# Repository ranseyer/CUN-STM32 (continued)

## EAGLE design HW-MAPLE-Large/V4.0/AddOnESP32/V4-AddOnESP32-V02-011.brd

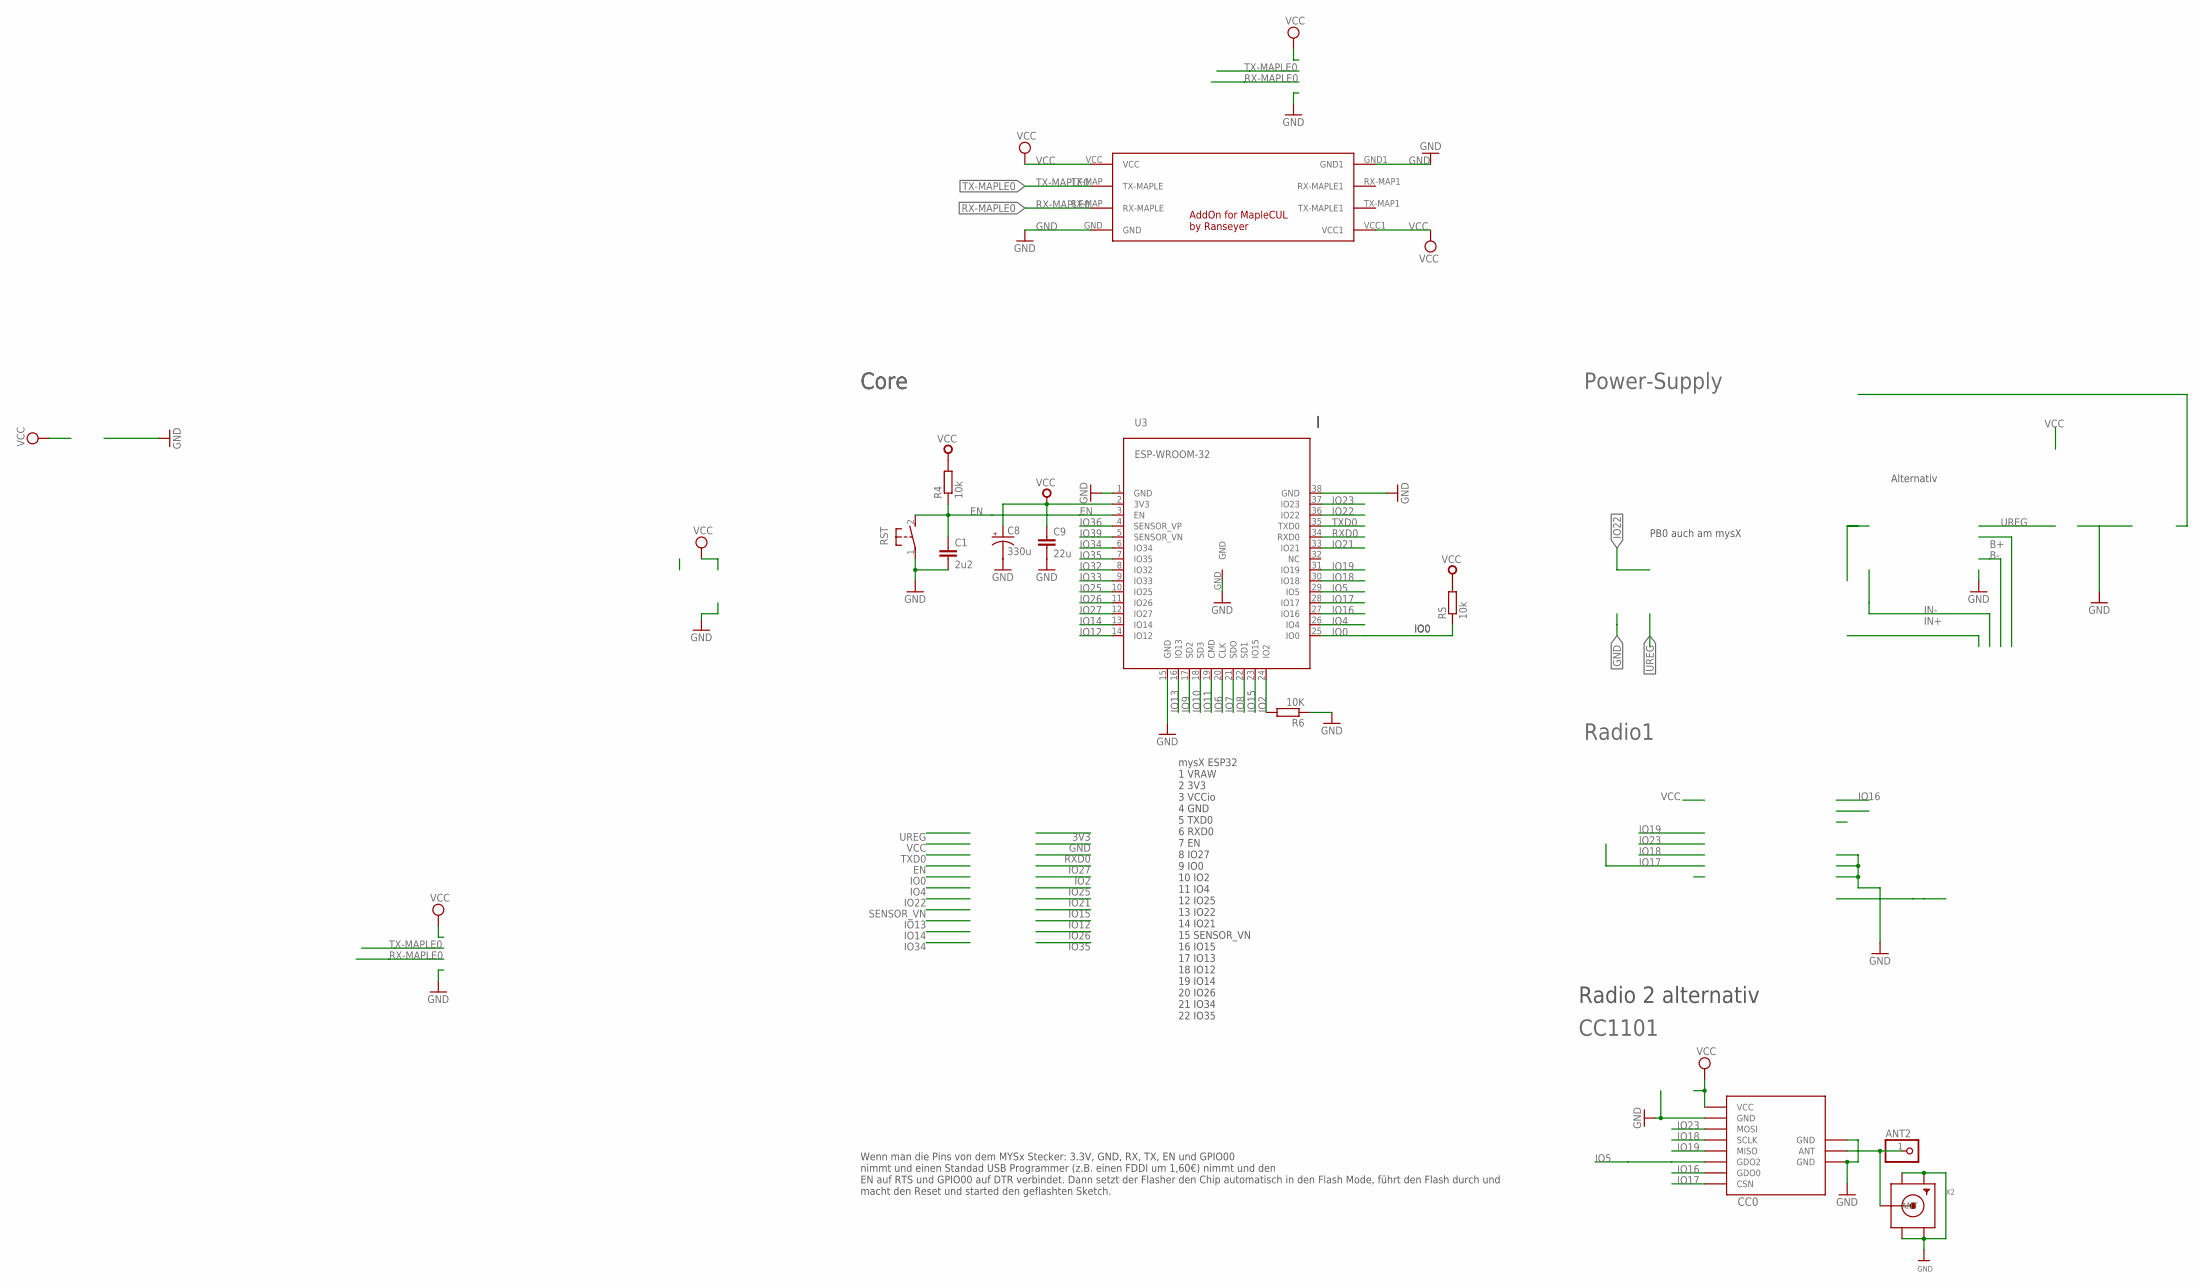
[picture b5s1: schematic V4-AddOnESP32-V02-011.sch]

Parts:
ANT2: PINHD-1X1; 1X01
C1: 2u2; C0805
C8: 330u; VISHAY_C
C9: 22u; C0805
CC0: CC1101; CC1101_MODULE1_SMD
R4, R5: 10k; M0805
R6: 10K; M0805
RST: DTSM-3
U3: ESP-WROOM-32
U$2: MAPLE-CUL-ADDON-V01; MAPLE-CUL-V01
X2: SMACONNECTOR_EDGE; SMA_EDGELAUNCH

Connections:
ANT0: ANT2.1, CC0.ANT, X2.P (ANT)
EN: C1.1, R4.1, RST.2, U3.3 (EN)
GND: C1.2, C8.-, C9.2, CC0.GND@0 (GND), CC0.GND@1 (GND), CC0.GND@2 (GND), R6.1, RST.1, U3.1 (GND), U3.15 (GND), U3.38 (GND), U3.GND, U$2.GND, U$2.GND1, X2.GND@1 (GND4), X2.GND@2 (GND3), X2.GND@3 (GND2), X2.GND@4 (GND1)
IO0: R5.1, U3.25 (IO0)
IO2: R6.2, U3.24 (IO2)
IO4: U3.26 (IO4)
IO5: CC0.GDO2, U3.29 (IO5)
IO6: U3.20 (CLK)
IO7: U3.21 (SDO)
IO8: U3.22 (SD1)
IO9: U3.17 (SD2)
IO10: U3.18 (SD3)
IO11: U3.19 (CMD)
IO12: U3.14 (IO12)
IO13: U3.16 (IO13)
IO14: U3.13 (IO14)
IO15: U3.23 (IO15)
IO16: CC0.GDO0, U3.27 (IO16)
IO17: CC0.CSN, U3.28 (IO17)
IO18: CC0.SCLK, U3.30 (IO18)
IO19: CC0.MISO, U3.31 (IO19)
IO21: U3.33 (IO21)
IO22: U3.36 (IO22)
IO23: CC0.MOSI, U3.37 (IO23)
IO25: U3.10 (IO25)
IO26: U3.11 (IO26)
IO27: U3.12 (IO27)
IO32: U3.8 (IO32)
IO33: U3.9 (IO33)
IO34: U3.6 (IO34)
IO35: U3.7 (IO35)
IO36: U3.4 (SENSOR_VP)
IO39: U3.5 (SENSOR_VN)
RX-MAPLE0: U$2.RX-MAP (RX-MAPLE)
RXD0: U3.34 (RXD0)
TX-MAPLE0: U$2.TX-MAP (TX-MAPLE)
TXD0: U3.35 (TXD0)
VCC: C8.+, C9.1, CC0.VCC, R4.2, R5.2, U3.2 (3V3), U$2.VCC, U$2.VCC1

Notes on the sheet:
mysX ESP32 1 VRAW 2 3V3 3 VCCio 4 GND 5 TXD0 6 RXD0 7 EN 8 IO27 9 IO0 10 IO2 11 IO4 12 IO25 13 IO22 14 IO21 15 SENSOR_VN 16 IO15 17 IO13 18 IO12 19 IO14 20 IO26 21 IO34 22 IO35
PB0 auch am mysX
Radio1
Radio 2 alternativ
CC1101
Wenn man die Pins von dem MYSx Stecker: 3.3V, GND, RX, TX, EN und GPIO00 nimmt und einen Standad USB Programmer (z.B. einen FDDI um 1,60€) nimmt und den EN auf RTS und GPIO00 auf DTR verbindet. Dann setzt der Flasher den Chip automatisch in den Flash Mode, führt den Flash durch und macht den Reset 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
Alternativ
Core
Power-Supply

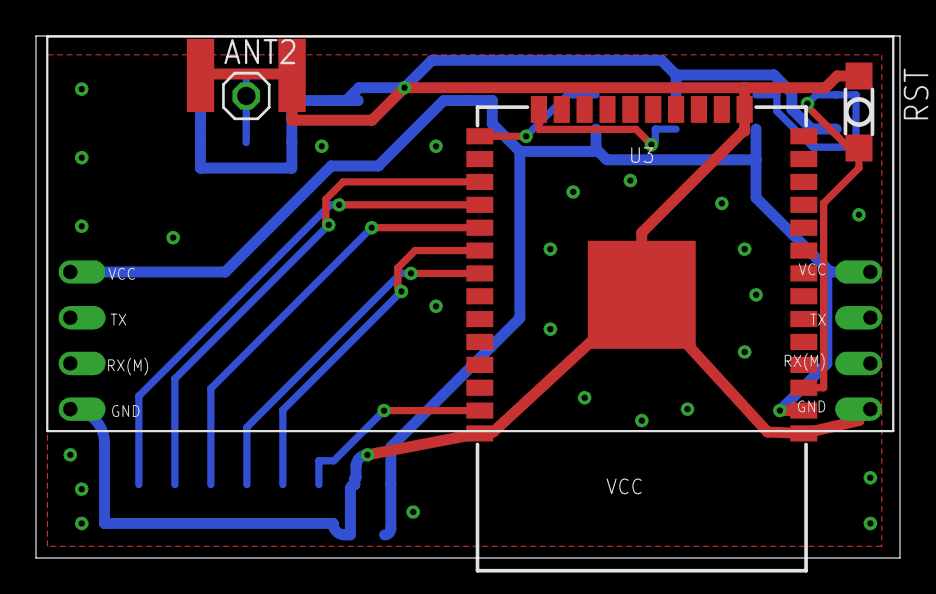
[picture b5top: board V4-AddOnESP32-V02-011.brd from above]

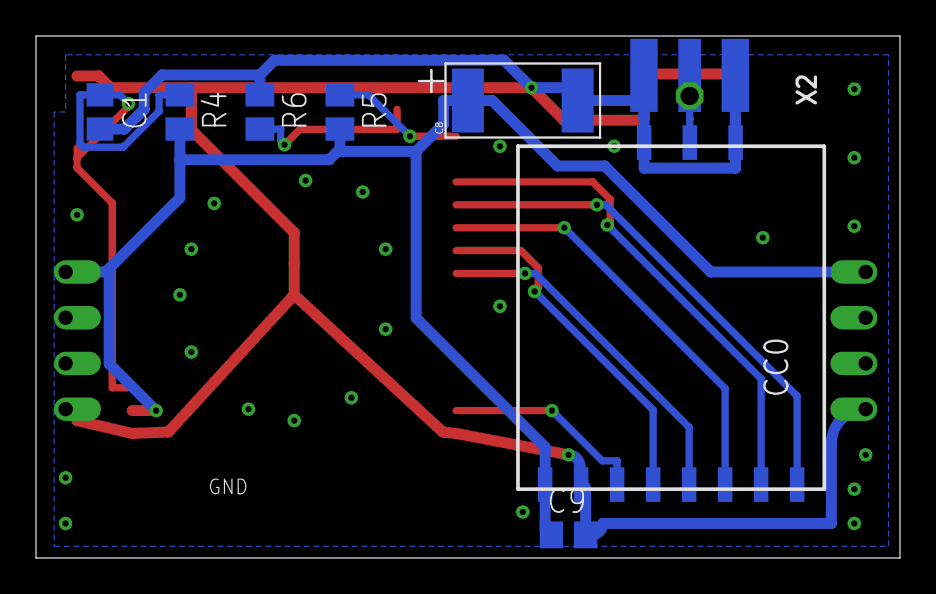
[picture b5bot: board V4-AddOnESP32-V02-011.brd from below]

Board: 2 copper layers, 48.0 x 29.0 mm, 12 parts (8 on the bottom side), 12 nets.

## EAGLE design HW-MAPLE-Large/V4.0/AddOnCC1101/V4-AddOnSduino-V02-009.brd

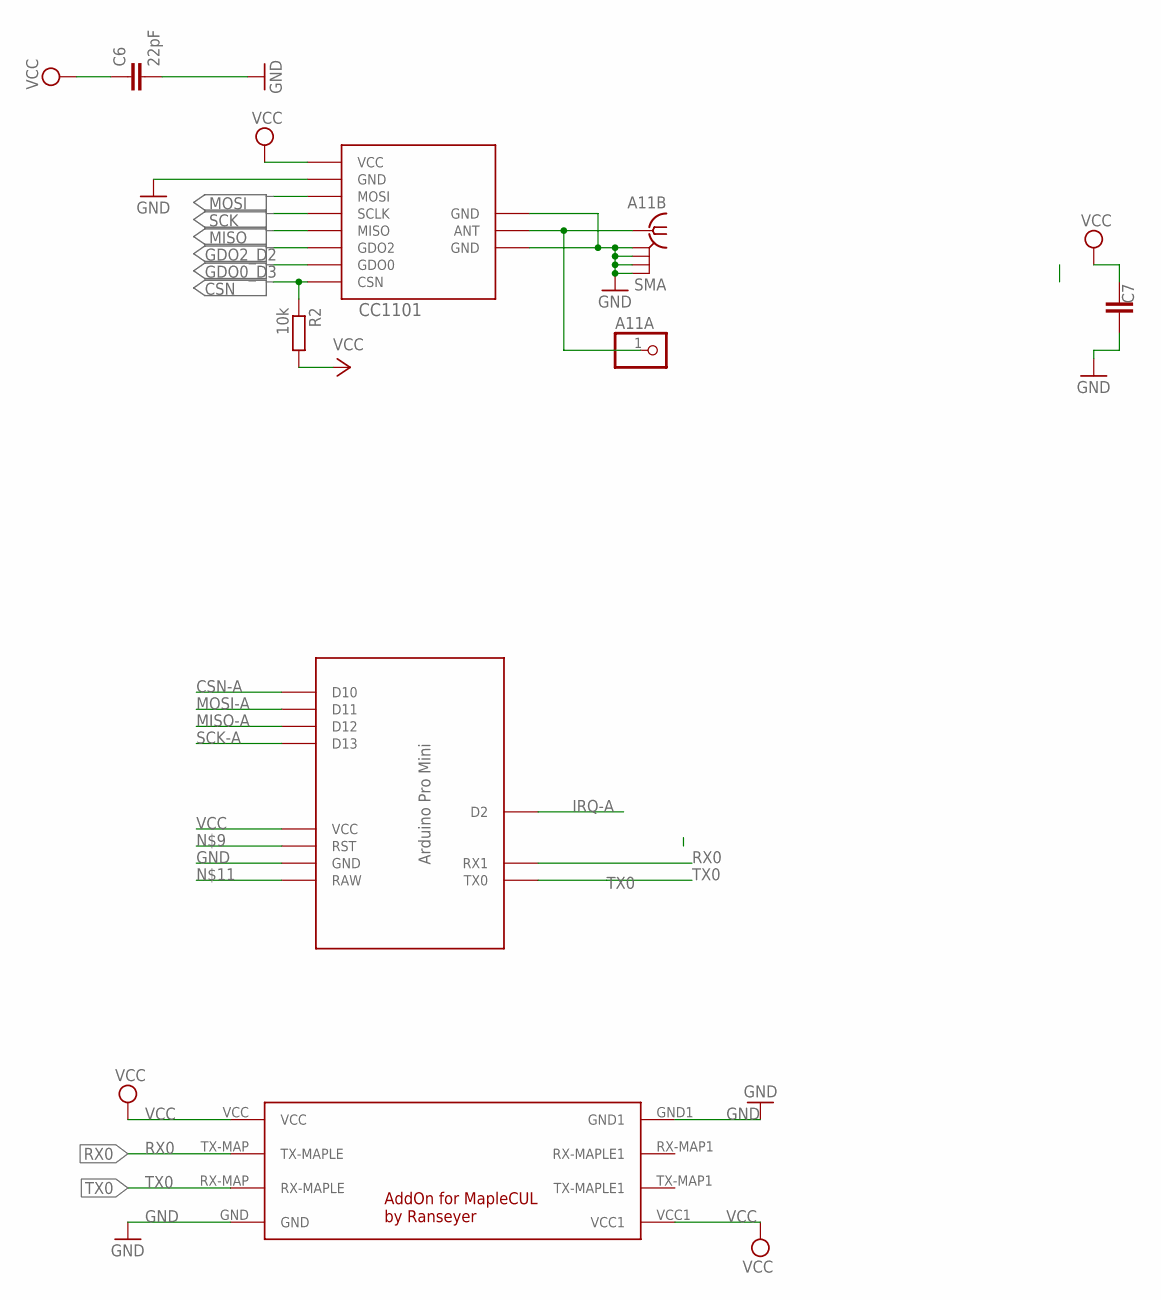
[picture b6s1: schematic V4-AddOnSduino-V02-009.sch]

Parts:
A11A: PINHD-1X1; 1X01
A11B: SMA
C6: 22pF; C0805
C7: C-EUC1812; C1812
CC1101: CC1101_MODULE1SMD; CC1101_MODULE1_SMD
R2: 10k; M0805
U$1: MARTIN-PROMINI-SPI; MARTIN-PRO-SPI
U$2: MAPLE-CUL-ADDON-V01; MAPLE-CUL-V01

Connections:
ANT2: A11A.1, A11B.1, CC1101.ANT
CSN: CC1101.CSN, R2.1
CSN-A: U$1.D10
GDO0_D3: CC1101.GDO0
GDO2_D2: CC1101.GDO2
GND: A11B.GND@1 (2), A11B.GND@2 (3), A11B.GND@3 (4), A11B.GND@4 (5), C6.2, C7.1, CC1101.GND@0 (GND), CC1101.GND@1 (GND), CC1101.GND@2 (GND), U$1.GND, U$2.GND, U$2.GND1
IRQ-A: U$1.D2
MISO: CC1101.MISO
MISO-A: U$1.D12
MOSI: CC1101.MOSI
MOSI-A: U$1.D11
RX0: U$1.RX1, U$2.TX-MAP (TX-MAPLE)
SCK: CC1101.SCLK
SCK-A: U$1.D13
TX0: U$1.TX0, U$2.RX-MAP (RX-MAPLE)
VCC: C6.1, C7.2, CC1101.VCC, R2.2, U$1.VCC, U$2.VCC, U$2.VCC1

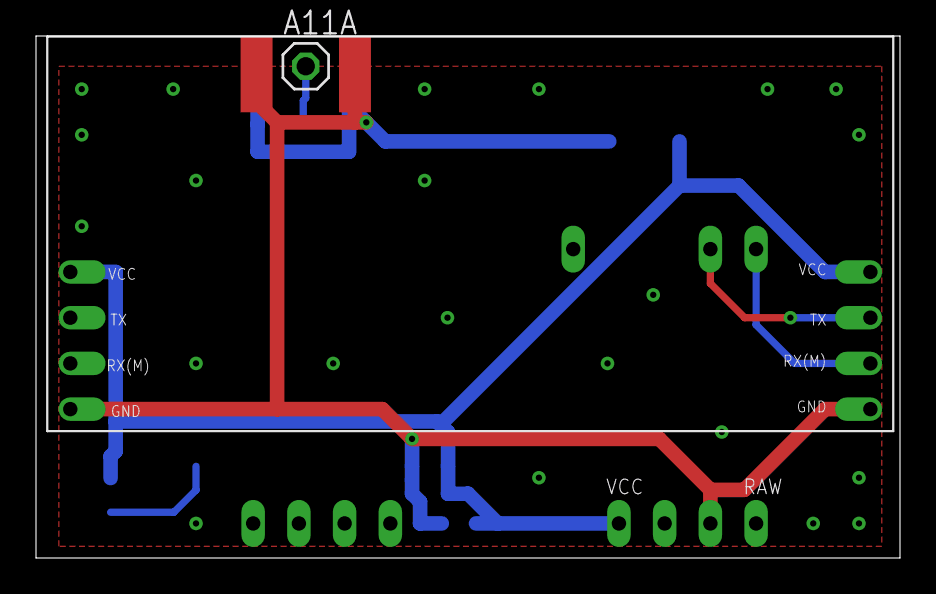
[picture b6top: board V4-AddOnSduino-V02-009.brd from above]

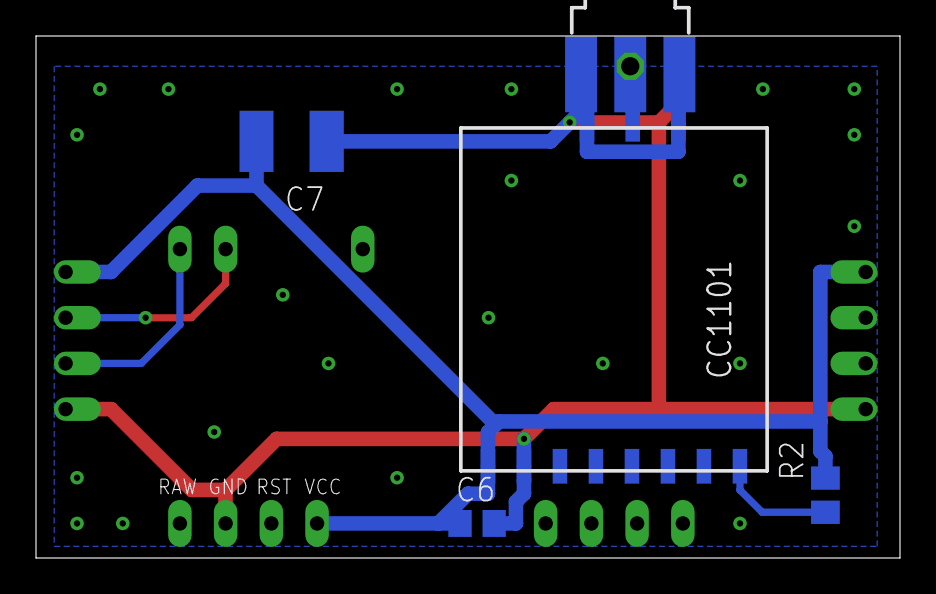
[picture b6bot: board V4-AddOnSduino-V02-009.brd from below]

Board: 2 copper layers, 48.0 x 29.0 mm, 8 parts (5 on the bottom side), 6 nets.

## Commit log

2016-12-20 1st draft
2016-12-21 Large Version V1
2016-12-27 Large Version V2
2016-12-28 Production Gerber
2017-02-02 Fix Large-PCB; Adapter for Stamps
2017-02-02 Moved LAN "Port"
2017-02-02 cleanup
2017-02-06 + mySensors
2017-02-06 optimized v2
2017-02-06 Folgende Änderungen: - bisheriges Layout im Raster 1 mm nach oben verschoben - Umrandung Gehäuse eingefügt - 433 MHz Modul im Schaltplan eingefügt - Arduino pro mini als Minimalversion in den Schaltp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
2017-02-07 Large A 1.2-Version
2017-02-08 v39, last complete file-set
2017-02-08 Medium V001
2017-02-08 Medium V001
    without Arduino-Board
2017-02-08 Cleanup + Restore V41-Schematic
2017-02-09 mapleCUx_003: - anderes Gehäuse - Bibliotheken für W5100 und W5500 Modul - Schaltplan aktualisiert - erste Platzierung Gruß PeMue
2017-02-14 Test in new case
2017-02-14 Large V41 as PNGs
2017-02-14 Cleanup2
2017-02-14 partlist
2017-02-15 U.FL Connectors possible
2017-02-16 New Version+ Cleanup
2017-02-18 Medium Test1
2017-02-27 v50 1Wire -draft
2017-02-27 v52 1Wire v2
2017-02-28 Large 056
2017-03-01 geänderte Version 57: - Beschriftungen angepasst (top/bottom) offen: - rechts über der Platine: Beschriftungen ggf. auf die Platine verschieben oder löschen - CC1101 Modul hat Beschriftung >Label -> 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
2017-03-02 Large 067
2017-03-02 Large 069 Maple moved to Bottom...
2017-03-03 korrigierte Bibliothek ohne >LABEL
2017-03-03 Large 082 Maple moved to Top...
2017-03-03 Large 083 Antennas rerouted
2017-03-03 Large 084 LAN lib fixed (dimension)
2017-03-03 MAPLE wieder unten
2017-03-04 Cleanup + Stripped Version
2017-03-04 Small Fixes + other RX+TX Pins at Arduino
2017-03-05 Charge4 in Archiv
2017-03-09 Restore Small-Version
2017-03-11 Medium-Version Draft
2017-04-09 Large 100 - small Optimisations
    -W5500 an Rand
    -UART mehr an Rand
    -ohne 1Wire
    - CC0+1 nicht mehr steckbar, nur Stamp
    -MAPLE oben, ober falls unter Buttons per Loch erreichbar
2017-04-09 Large 102
2017-04-11 Small Version
2017-04-22 1.2 Large - more docu
2017-04-26 Stamp-Adapter-Mini Version
2017-04-27 Mini-Stamp-Adapter
2017-05-12 V2 Large, Small-Update
2017-09-27 Docs V2.1
2017-10-08 Docs V2.0
2017-10-17 V3.0 (stripped) plus Addon
2017-12-09 Pictures + Fixes
2017-12-15 V3 Update + AddOns
    V3 => 3.1 some more Cs
    Addons:
    -OneWire Beta
    -RFM69: Module with other / better Footprint
2017-12-17 AddOn update
2017-12-20 Addon: plus RFM95
2017-12-22 Update RFM95, etc.
2017-12-22 Docu
2018-05-04 V3.2
2018-05-05 export of "Small" docu
2018-05-18 Backlink to CADLAB.io has been added.
2018-06-11 Large 3.3 + AddOn for Raspi-UART-Modules
2018-06-13 V3.3 large
2018-07-02 Raspi + Zigbee
2018-07-29 Case from Thingiverse; Zigbee/RaspiAddOn
2018-08-07 Small + Zigbee
2018-08-08 Zigbee TX Fix
2018-10-26 V3.4
2018-11-17 Zigbee
2018-12-02 v02 export
2018-12-27 LARGE PCB SMD-Cap
2018-12-27 Schematic
2019-01-06 Docs
2019-02-17 V3.5
    2 more Connections to ESP
    Port for flashing, 1Wire
2019-02-17 LAN AddOn
2019-02-22 V3.5 and 1W Stamp
2019-02-22 1W-UART
2019-02-22 OneWire
2019-02-22 Reorg Dirs
2019-03-07 1.4 docs
2019-03-26 Zigbee Addon 0.4
2019-03-27 V4 first draft
2019-04-13 V4 Test
2019-05-12 1Wire and others
2019-05-29 Fix for old RFM69 AddOn + Docu
2019-06-23 Carrier-Board + AddOns
2019-06-23 Carrier
2019-07-03 V4 General Update
2019-07-29 V4-AddOns ; Large
2019-08-03 Fotos
